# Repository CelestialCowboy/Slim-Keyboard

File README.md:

# Slim-Keyboard

A custom keyboard designed for a compacts layout with a slim profile.   
Operates on an Rpi-Pico running 'Circuit Python'

**Critical Hardware:**  
<table>
  <tr>
    <td>

<!-- Markdown table goes here -->
  
| Item                                   | Quantity |
|----------------------------------------|----------|
| Gateron Low Profile Key Switch Blue    | 97       |
| 1N914 Diode                            | 97       |
| Custom PCM                             | 1        |
| Rpi Pico                               | 1        |
| Rotary Encoder - SW-PEC11R-4215F-S0024 | 1        |
| 10kR TH Resistor                       | 2        |
| M3 x 8 Bolt                            | 5        |
| M3 Brass Heatsert                      | 5        |
| Micro USB Cable                        | 1        |
| Keycaps                                | 97       |

  </td>
  <td>
    
  </td>
  </tr>
</table>

**Product:**  

**PCB:**

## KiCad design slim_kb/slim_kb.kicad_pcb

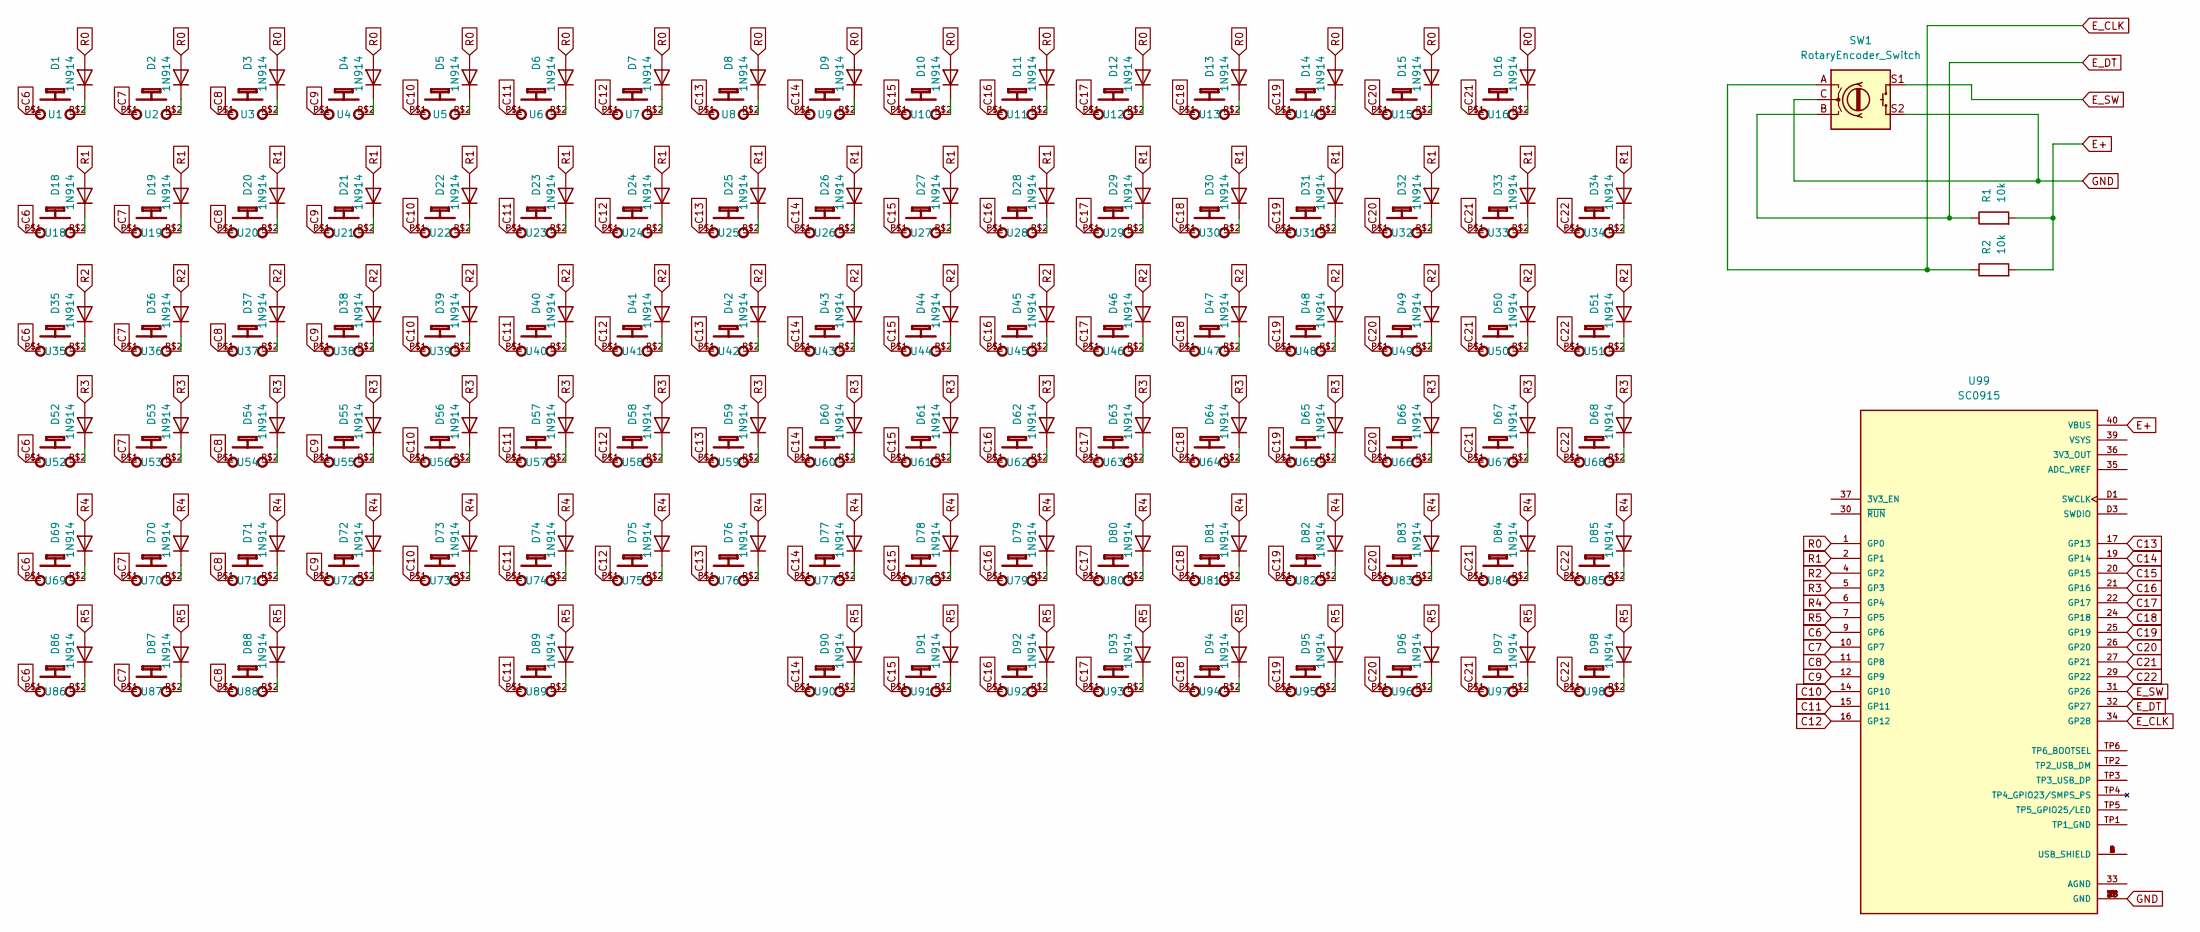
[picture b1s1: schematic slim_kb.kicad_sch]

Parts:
D1, D2, D3, D4, D5, D6, D7, D8, D9, D10, D11, D12, D13, D14, D15, D16, D18, D19, D20, D21, D22, D23, D24, D25, D26, D27, D28, D29, D30, D31, D32, D33, D34, D35, D36, D37, D38, D39, D40, D41, D42, D43, D44, D45, D46, D47, D48, D49, D50, D51, D52, D53, D54, D55, D56, D57, D58, D59, D60, D61, D62, D63, D64, D65, D66, D67, D68, D69, D70, D71, D72, D73, D74, D75, D76, D77, D78, D79, D80, D81, D82, D83, D84, D85, D86, D87, D88, D89, D90, D91, D92, D93, D94, D95, D96, D97, D98: 1N914; D_DO-35_SOD27_P7.62mm_Horizontal
R1, R2: 10k; R_Axial_DIN0207_L6.3mm_D2.5mm_P10.16mm_Horizontal
SW1: RotaryEncoder_Switch; RotaryEncoder_Alps_EC12E-Switch_Vertical_H20mm
U1, U2, U3, U4, U5, U6, U7, U8, U9, U10, U11, U12, U13, U14, U15, U16, U18, U19, U20, U21, U22, U23, U24, U25, U26, U27, U28, U29, U30, U31, U32, U33, U34, U35, U36, U37, U38, U39, U40, U41, U42, U43, U44, U45, U46, U47, U48, U49, U50, U51, U52, U53, U54, U55, U56, U57, U58, U59, U60, U61, U62, U63, U64, U65, U66, U67, U68, U69, U70, U71, U72, U73, U74, U75, U76, U77, U78, U79, U80, U81, U82, U83, U84, U85, U86, U87, U88, U89, U90, U91, U92, U93, U94, U95, U96, U97, U98: CHERRY_MX1A-11NN_SWITCH
U99: SC0915; MODULE_SC0915; PARTREV 1.9

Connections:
C6: U1.P$1, U18.P$1, U35.P$1, U52.P$1, U69.P$1, U86.P$1, U99.9 (GP6)
C7: U2.P$1, U19.P$1, U36.P$1, U53.P$1, U70.P$1, U87.P$1, U99.10 (GP7)
C8: U3.P$1, U20.P$1, U37.P$1, U54.P$1, U71.P$1, U88.P$1, U99.11 (GP8)
C9: U4.P$1, U21.P$1, U38.P$1, U55.P$1, U72.P$1, U99.12 (GP9)
C10: U5.P$1, U22.P$1, U39.P$1, U56.P$1, U73.P$1, U99.14 (GP10)
C11: U6.P$1, U23.P$1, U40.P$1, U57.P$1, U74.P$1, U89.P$1, U99.15 (GP11)
C12: U7.P$1, U24.P$1, U41.P$1, U58.P$1, U75.P$1, U99.16 (GP12)
C13: U8.P$1, U25.P$1, U42.P$1, U59.P$1, U76.P$1, U99.17 (GP13)
C14: U9.P$1, U26.P$1, U43.P$1, U60.P$1, U77.P$1, U90.P$1, U99.19 (GP14)
C15: U10.P$1, U27.P$1, U44.P$1, U61.P$1, U78.P$1, U91.P$1, U99.20 (GP15)
C16: U11.P$1, U28.P$1, U45.P$1, U62.P$1, U79.P$1, U92.P$1, U99.21 (GP16)
C17: U12.P$1, U29.P$1, U46.P$1, U63.P$1, U80.P$1, U93.P$1, U99.22 (GP17)
C18: U13.P$1, U30.P$1, U47.P$1, U64.P$1, U81.P$1, U94.P$1, U99.24 (GP18)
C19: U14.P$1, U31.P$1, U48.P$1, U65.P$1, U82.P$1, U95.P$1, U99.25 (GP19)
C20: U15.P$1, U32.P$1, U49.P$1, U66.P$1, U83.P$1, U96.P$1, U99.26 (GP20)
C21: U16.P$1, U33.P$1, U50.P$1, U67.P$1, U84.P$1, U97.P$1, U99.27 (GP21)
C22: U34.P$1, U51.P$1, U68.P$1, U85.P$1, U98.P$1, U99.29 (GP22)
E+: R1.2, R2.2, U99.40 (VBUS)
E_CLK: R2.1, SW1.A, U99.34 (GP28)
E_DT: R1.1, SW1.B, U99.32 (GP27)
E_SW: SW1.S1, U99.31 (GP26)
GND: SW1.C, SW1.S2, U99.3 (GND), U99.8 (GND), U99.13 (GND), U99.18 (GND), U99.23 (GND), U99.28 (GND), U99.38 (GND), U99.D2 (GND)
unnamed: D1.1 (K), U1.P$2
unnamed: D2.1 (K), U2.P$2
unnamed: D3.1 (K), U3.P$2
unnamed: D4.1 (K), U4.P$2
unnamed: D5.1 (K), U5.P$2
unnamed: D6.1 (K), U6.P$2
unnamed: D7.1 (K), U7.P$2
unnamed: D8.1 (K), U8.P$2
unnamed: D9.1 (K), U9.P$2
unnamed: D10.1 (K), U10.P$2
unnamed: D11.1 (K), U11.P$2
unnamed: D12.1 (K), U12.P$2
unnamed: D13.1 (K), U13.P$2
unnamed: D14.1 (K), U14.P$2
unnamed: D15.1 (K), U15.P$2
unnamed: D16.1 (K), U16.P$2
unnamed: D18.1 (K), U18.P$2
unnamed: D19.1 (K), U19.P$2
unnamed: D20.1 (K), U20.P$2
unnamed: D21.1 (K), U21.P$2
unnamed: D22.1 (K), U22.P$2
unnamed: D23.1 (K), U23.P$2
unnamed: D24.1 (K), U24.P$2
unnamed: D25.1 (K), U25.P$2
unnamed: D26.1 (K), U26.P$2
unnamed: D27.1 (K), U27.P$2
unnamed: D28.1 (K), U28.P$2
unnamed: D29.1 (K), U29.P$2
unnamed: D30.1 (K), U30.P$2
unnamed: D31.1 (K), U31.P$2
unnamed: D32.1 (K), U32.P$2
unnamed: D33.1 (K), U33.P$2
unnamed: D34.1 (K), U34.P$2
unnamed: D35.1 (K), U35.P$2
unnamed: D36.1 (K), U36.P$2
unnamed: D37.1 (K), U37.P$2
unnamed: D38.1 (K), U38.P$2
unnamed: D39.1 (K), U39.P$2
unnamed: D40.1 (K), U40.P$2
unnamed: D41.1 (K), U41.P$2
unnamed: D42.1 (K), U42.P$2
unnamed: D43.1 (K), U43.P$2
unnamed: D44.1 (K), U44.P$2
unnamed: D45.1 (K), U45.P$2
unnamed: D46.1 (K), U46.P$2
unnamed: D47.1 (K), U47.P$2
unnamed: D48.1 (K), U48.P$2
unnamed: D49.1 (K), U49.P$2
unnamed: D50.1 (K), U50.P$2
unnamed: D51.1 (K), U51.P$2
unnamed: D52.1 (K), U52.P$2
unnamed: D53.1 (K), U53.P$2
unnamed: D54.1 (K), U54.P$2
unnamed: D55.1 (K), U55.P$2
unnamed: D56.1 (K), U56.P$2
unnamed: D57.1 (K), U57.P$2
unnamed: D58.1 (K), U58.P$2
unnamed: D59.1 (K), U59.P$2
unnamed: D60.1 (K), U60.P$2
unnamed: D61.1 (K), U61.P$2
unnamed: D62.1 (K), U62.P$2
unnamed: D63.1 (K), U63.P$2
unnamed: D64.1 (K), U64.P$2
unnamed: D65.1 (K), U65.P$2
unnamed: D66.1 (K), U66.P$2
unnamed: D67.1 (K), U67.P$2
unnamed: D68.1 (K), U68.P$2
unnamed: D69.1 (K), U69.P$2
unnamed: D70.1 (K), U70.P$2
unnamed: D71.1 (K), U71.P$2
unnamed: D72.1 (K), U72.P$2
unnamed: D73.1 (K), U73.P$2
unnamed: D74.1 (K), U74.P$2
unnamed: D75.1 (K), U75.P$2
unnamed: D76.1 (K), U76.P$2
unnamed: D77.1 (K), U77.P$2
unnamed: D78.1 (K), U78.P$2
unnamed: D79.1 (K), U79.P$2
unnamed: D80.1 (K), U80.P$2
unnamed: D81.1 (K), U81.P$2
unnamed: D82.1 (K), U82.P$2
unnamed: D83.1 (K), U83.P$2
unnamed: D84.1 (K), U84.P$2
unnamed: D85.1 (K), U85.P$2
unnamed: D86.1 (K), U86.P$2
unnamed: D87.1 (K), U87.P$2
unnamed: D88.1 (K), U88.P$2
unnamed: D89.1 (K), U89.P$2
unnamed: D90.1 (K), U90.P$2
unnamed: D91.1 (K), U91.P$2
unnamed: D92.1 (K), U92.P$2
unnamed: D93.1 (K), U93.P$2
unnamed: D94.1 (K), U94.P$2
unnamed: D95.1 (K), U95.P$2
unnamed: D96.1 (K), U96.P$2
unnamed: D97.1 (K), U97.P$2
unnamed: D98.1 (K), U98.P$2
unnamed: U99.A (USB_SHIELD), U99.B (USB_SHIELD), U99.C (USB_SHIELD), U99.D (USB_SHIELD)
R0: D1.2 (A), D2.2 (A), D3.2 (A), D4.2 (A), D5.2 (A), D6.2 (A), D7.2 (A), D8.2 (A), D9.2 (A), D10.2 (A), D11.2 (A), D12.2 (A), D13.2 (A), D14.2 (A), D15.2 (A), D16.2 (A), U99.1 (GP0)
R1: D18.2 (A), D19.2 (A), D20.2 (A), D21.2 (A), D22.2 (A), D23.2 (A), D24.2 (A), D25.2 (A), D26.2 (A), D27.2 (A), D28.2 (A), D29.2 (A), D30.2 (A), D31.2 (A), D32.2 (A), D33.2 (A), D34.2 (A), U99.2 (GP1)
R2: D35.2 (A), D36.2 (A), D37.2 (A), D38.2 (A), D39.2 (A), D40.2 (A), D41.2 (A), D42.2 (A), D43.2 (A), D44.2 (A), D45.2 (A), D46.2 (A), D47.2 (A), D48.2 (A), D49.2 (A), D50.2 (A), D51.2 (A), U99.4 (GP2)
R3: D52.2 (A), D53.2 (A), D54.2 (A), D55.2 (A), D56.2 (A), D57.2 (A), D58.2 (A), D59.2 (A), D60.2 (A), D61.2 (A), D62.2 (A), D63.2 (A), D64.2 (A), D65.2 (A), D66.2 (A), D67.2 (A), D68.2 (A), U99.5 (GP3)
R4: D69.2 (A), D70.2 (A), D71.2 (A), D72.2 (A), D73.2 (A), D74.2 (A), D75.2 (A), D76.2 (A), D77.2 (A), D78.2 (A), D79.2 (A), D80.2 (A), D81.2 (A), D82.2 (A), D83.2 (A), D84.2 (A), D85.2 (A), U99.6 (GP4)
R5: D86.2 (A), D87.2 (A), D88.2 (A), D89.2 (A), D90.2 (A), D91.2 (A), D92.2 (A), D93.2 (A), D94.2 (A), D95.2 (A), D96.2 (A), D97.2 (A), D98.2 (A), U99.7 (GP5)

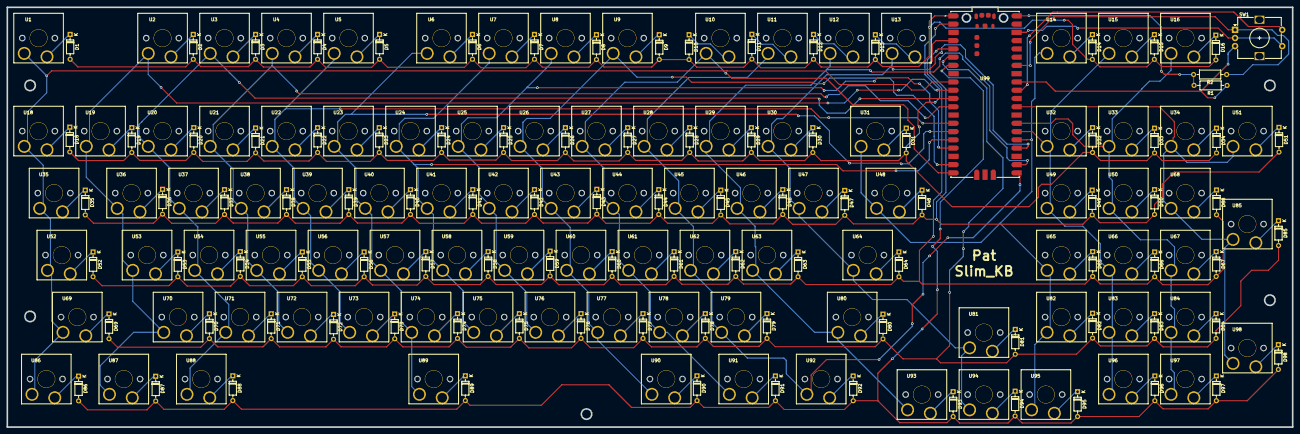
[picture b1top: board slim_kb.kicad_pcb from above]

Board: 2 copper layers, 395.0 x 129.0 mm, 198 parts (0 on the bottom side), 126 nets.
